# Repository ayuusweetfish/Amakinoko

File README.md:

# 天气蘑菇 · アマキノコ · Amakinoko

一个蘑菇外形的彩灯装置，流动的颜色依天气变化。光效亦可通过 USB 连接电脑定制。

[**汇报展示与视频**](https://ayuusweetfish.github.io/Amakinoko/)  
[**Rev. 2 资料**](https://github.com/ayuusweetfish/Amakinoko/releases/tag/rev-2)

## 食谱

材料
- 3D 打印外壳元件
- 炫彩纱布（？）
- WS2812/WS2812B 灯带（5050 灯珠；每米 96 灯，取 24 灯）
- 2.54 mm 排针
- 2.54 mm 跳线（杜邦线），双端孔头
- 组装电路板（PCBA）
- 胶水，如 UHU 胶
- （可选）热熔胶
- （可选）镀银纱线

步骤
1. 将纱布用胶水粘贴在两片外壳上；
2. 将 3 pin 排针焊接在灯带首端；
3. 将灯带打结成球状，尽可能使每一个朝向都有小灯；
4. 将灯带上的排针插入杜邦线，连接至电路板；
5. 将灯带与杜邦线固定在内胆内侧（可用胶水或热熔胶），保持灯带悬空在中央位置；
6. （可选）若有镀银纱线，可将其随意粘贴在外壳内壁，另一端穿过电路板上的触摸传感孔，打结、粘贴固定；
7. 将外壳与内胆粘贴固定；
8. 连接 USB 电源即可。

注：3D 打印与 PCBA 的组装未列入。PCBA 组装可参考 KiCad 工程文件；完成后通过 DAP 调试器向 STM32 微控制器写入固件，再通过蘑菇配置工具写入灯光程序。

## 定制灯光

通过 USB 数据线将装置连接至计算机，运行配置工具软件（发布页面提供 Windows 与 macOS 版本下载）。连接后即可看到实时读数、灯光颜色与光效程序。

光效程序运行在 [Mumu 虚拟机](./misc/mumu)中，目前以 Mumu 汇编语言撰写。Mumu 是一个结构简单的虚拟计算模型，其上的程序能访问 2 KiB 的内存空间。

## 目录组织
- **hw/**: 印刷电路板工程文件
- **fw/**: STM32 微控制器固件源程序
- **mech/**: 外壳 3D 模型
- **cfg/**: PC 配置工具软件源程序

部分文件可以通过以下软件打开（版本号作为参考）：
- 外壳：3D One
- 电路板：KiCad (7.0.10)
- 固件：Arm GNU Toolchain (GCC 10.3.1), STM32CubeG0 (1.5.0), PlatformIO (6.1.16)

## 许可

本仓库内的所有内容按照 CERN-OHL-S（CERN 开放硬件许可证第 2 版，强互惠条件）分发。完整原文参见 **COPYING.txt** 或[在线访问](https://ohwr.org/cern_ohl_s_v2.txt)。

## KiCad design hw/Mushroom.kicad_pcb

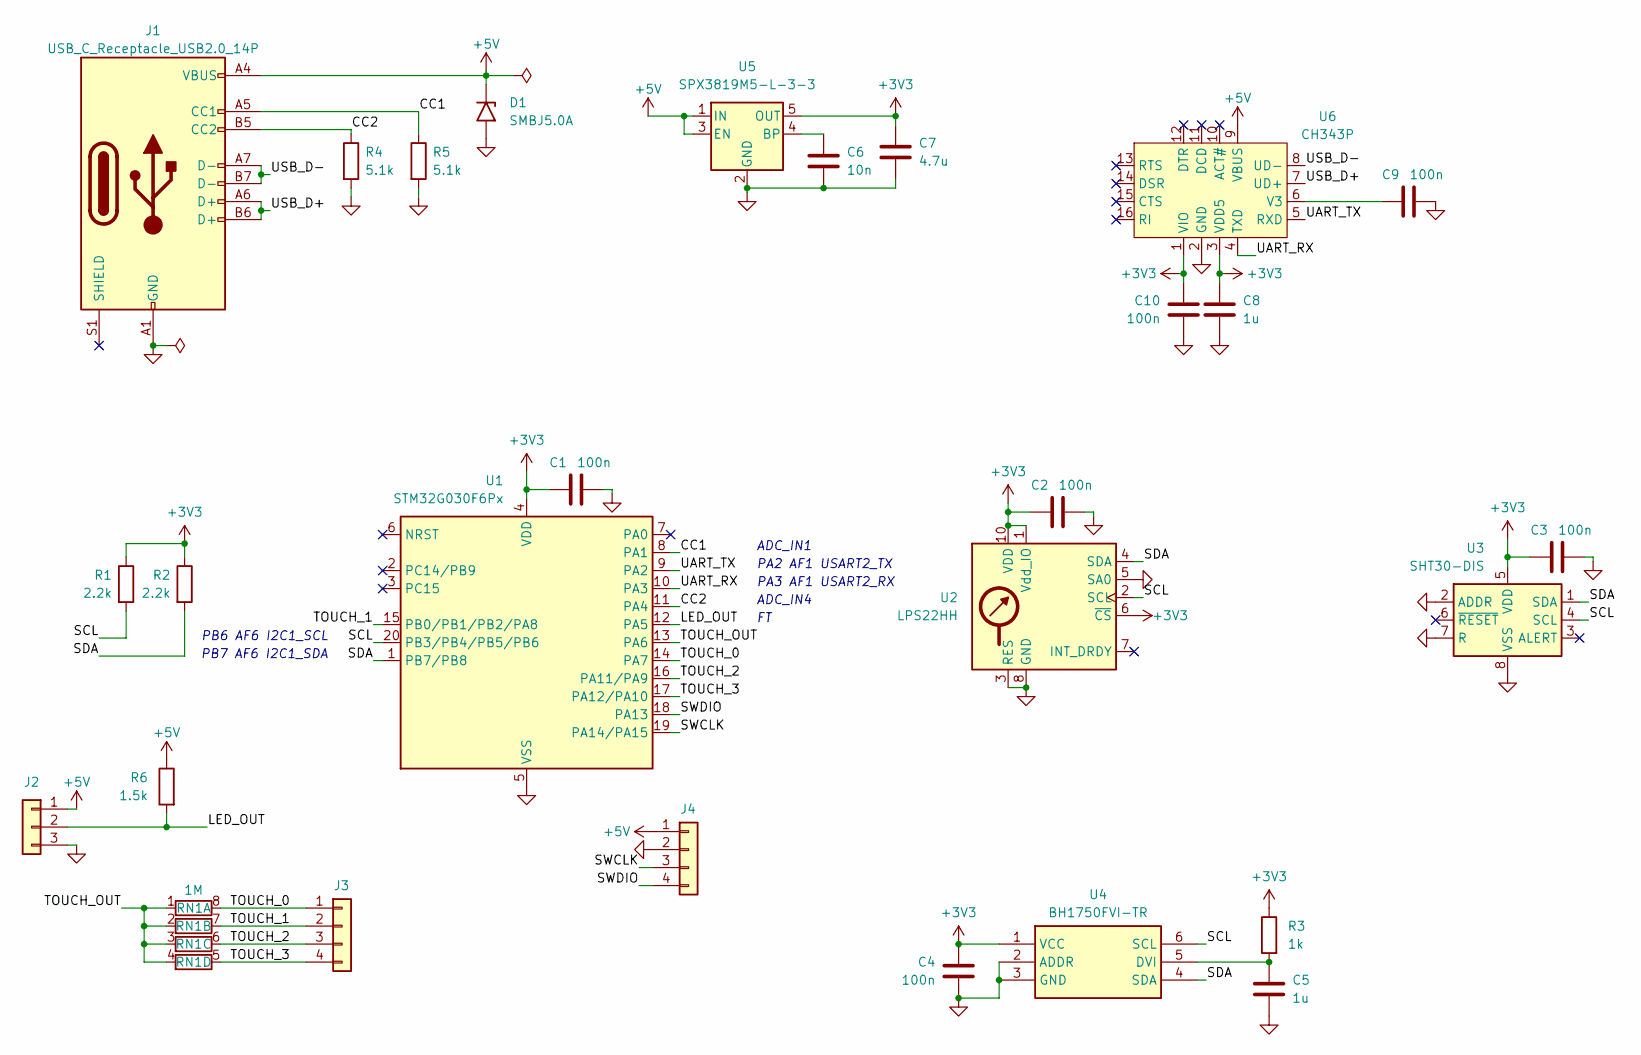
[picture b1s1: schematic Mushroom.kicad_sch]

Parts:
C1, C2, C3, C4, C9, C10: 100n; C_0402_1005Metric
C5, C8: 1u; C_0402_1005Metric
C6: 10n; C_0402_1005Metric
C7: 4.7u; C_0402_1005Metric
D1: SMBJ5.0A; D_SMB
J1: USB_C_Receptacle_USB2.0_14P; USB_C_Receptacle_HRO_TYPE-C-31-M-12
J2: Conn_01x03; PinHeader_1x03_P2.54mm_Vertical
J3: Conn_01x04; Arc_Pins_04
J4: Conn_01x04; TestPoints_1x04_P2.0
R1, R2: 2.2k; R_0402_1005Metric
R3: 1k; R_0402_1005Metric
R4, R5: 5.1k; R_0402_1005Metric
R6: 1.5k; R_0402_1005Metric
RN1: 1M; R_Array_Convex_4x0402
U1: STM32G030F6Px; TSSOP-20_4.4x6.5mm_P0.65mm
U2: LPS22HH; ST_HLGA-10_2x2mm_P0.5mm_LayoutBorder3x2y
U3: SHT30-DIS; Sensirion_DFN-8-1EP_2.5x2.5mm_P0.5mm_EP1.1x1.7mm
U4: BH1750FVI-TR; WSOF6; Manufacturer_Part_Number BH1750FVI-TR; Mouser Part Number 755-BH1750FVI-TR
U5: SPX3819M5-L-3-3; SOT-23-5
U6: CH343P; QFN-16-1EP_3x3mm_P0.5mm_EP1.9x1.9mm

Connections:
+3V3: C1.1, C2.1, C3.1, C4.1, C7.1, C8.1, C10.1, R1.1, R2.1, R3.1, U1.4 (VDD), U2.1 (Vdd_IO), U2.6 (~CS), U2.10 (VDD), U3.5 (VDD), U4.1 (VCC), U5.5 (OUT), U6.1 (VIO), U6.3 (VDD5)
+5V: D1.1 (A1), J1.A4 (VBUS), J1.A9 (VBUS), J1.B4 (VBUS), J1.B9 (VBUS), J2.1, J4.1, R6.1, U5.1 (IN), U5.3 (EN), U6.9 (VBUS)
/CC1: J1.A5 (CC1), R5.1, U1.8 (PA1)
/CC2: J1.B5 (CC2), R4.1, U1.11 (PA4)
/LED_OUT: J2.2, R6.2, U1.12 (PA5)
/SCL: R1.2, U1.20 (PB3/PB4/PB5/PB6), U2.2 (SCL), U3.4 (SCL), U4.6 (SCL)
/SDA: R2.2, U1.1 (PB7/PB8), U2.4 (SDA), U3.1 (SDA), U4.4 (SDA)
/SWCLK: J4.3, U1.19 (PA14/PA15)
/SWDIO: J4.4, U1.18 (PA13)
/TOUCH_0: J3.1, RN1.8 (R1.2), U1.14 (PA7)
/TOUCH_1: J3.2, RN1.7 (R2.2), U1.15 (PB0/PB1/PB2/PA8)
/TOUCH_2: J3.3, RN1.6 (R3.2), U1.16 (PA11/PA9)
/TOUCH_3: J3.4, RN1.5 (R4.2), U1.17 (PA12/PA10)
/TOUCH_OUT: RN1.1 (R1.1), RN1.2 (R2.1), RN1.3 (R3.1), RN1.4 (R4.1), U1.13 (PA6)
/UART_RX: U1.10 (PA3), U6.4 (TXD)
/UART_TX: U1.9 (PA2), U6.5 (RXD)
/USB_D+: J1.A6 (D+), J1.B6 (D+), U6.7 (UD+)
/USB_D-: J1.A7 (D-), J1.B7 (D-), U6.8 (UD-)
GND: C1.2, C2.2, C3.2, C4.2, C5.2, C6.2, C7.2, C8.2, C9.2, C10.2, D1.2 (A2), J1.A1 (GND), J1.A12 (GND), J1.B1 (GND), J1.B12 (GND), J2.3, J4.2, R4.2, R5.2, U1.5 (VSS), U2.3 (RES), U2.5 (SA0), U2.8 (GND), U2.9 (GND), U3.2 (ADDR), U3.7 (R), U3.8 (VSS), U3.9 (VSS), U4.2 (ADDR), U4.3 (GND), U5.2 (GND), U6.2 (GND), U6.17 (GND)
unnamed: C5.1, R3.2, U4.5 (DVI)
unnamed: C6.1, U5.4 (BP)
unnamed: C9.1, U6.6 (V3)

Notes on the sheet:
PB6 AF6 I2C1_SCL
PA2 AF1 USART2_TX
ADC_IN1
PA3 AF1 USART2_RX
ADC_IN4
PB7 AF6 I2C1_SDA

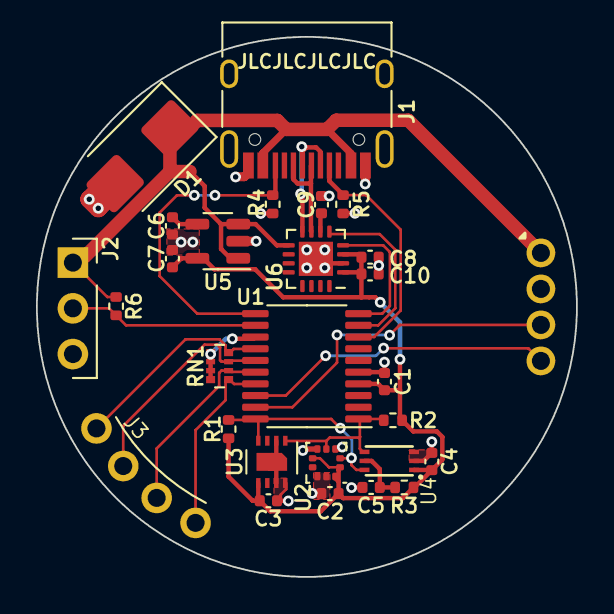
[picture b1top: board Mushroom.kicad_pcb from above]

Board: 2 copper layers, 30.0 x 30.0 mm, 28 parts (0 on the bottom side), 22 nets.

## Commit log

2024-10-16 🚧 Initial commit; empty hardware project
2024-10-18 Add testrun firmware (board is Curtain Rev. 1)
2024-10-19 Increase testrun light intensity & refresh rate
2024-10-21 Finish schematic
2024-10-21 🚧 Preliminary layout & routing
2024-10-21 Finish board design
2024-10-21 Revise and finalise board design
2024-10-21 🎉 Submit for fab (Rev. 1)
2024-10-21 Change board setup to white / 1 mm
2024-10-25 🎉 Initial firmware
2024-10-25 I2C SCL line stuck low?
2024-10-25 Toggle LED data output pin
2024-10-25 Restore I2C check
    Previous issue: BH1750FVI was soldered in the wrong direction
2024-10-25 ✨ Flowing lights!
2024-10-25 Fix I2C timing setting
2024-10-26 Read-out from LPS22HH
2024-10-26 Fix I2C bus stuck issue (output should be open-drain)
2024-10-26 Read-out from SHT30
2024-10-26 Revise board schematic
2024-10-26 Preliminary layout & routing
2024-10-26 🎉 Finalise design; submit for fab (Rev. 2)
2024-10-26 Fix TX/RX lines; re-submit for fab (Rev. 2)
    Previous order was cancelled (Y52, Y53)
2024-10-27 Clean-up of sensor-reading subroutine
2024-10-27 Incorporate sensor readings into the display loop
2024-10-27 Release WS2812 signal line when idle to avoid continuous draining current
2024-10-28 Implement capacitive sensing
2024-10-28 Incorporate capacitance sensing into main loop
2024-10-30 Add configuration GUI empty template
2024-10-30 Add Uxn in firmware
2024-10-30 Stress test Uxn
2024-10-31 🎉 A new VM??
2024-10-31 Optimise a bit 😈
2024-11-01 Computed goto (slower... T T)
2024-11-01 Small bug fixes
2024-11-01 Save new pattern generator for potential future demonstrations
2024-11-01 mumu: Implement load-store & branching instructions
2024-11-01 mumu: Fibonacci program
2024-11-01 mumu: Running Fibonacci on MCU
2024-11-01 mumu: Optimised Fibonacci
2024-11-01 mumu: Revise instruction set & documentation
2024-11-02 mumu: 🚧 Assembler
2024-11-02 mumu: 🚧 Parse mnemonics
2024-11-02 mumu: Parse all mnemonics and labels
2024-11-02 mumu: 🚧 Assemble most instructions
    TODO: memory, forward label patching
2024-11-02 mumu: 🎉 Assemble the Fibonacci program
2024-11-04 mumu: Correct platform-agnostic data width
2024-11-04 mumu-as: Refactor to report errors to caller routine
2024-11-04 mumu-as: Better error reporting
2024-11-04 mumu-as: Implement memory instructions
2024-11-04 mumu-as: Include column index in error report
2024-11-04 mumu-as: Support data directive
2024-11-04 mumu-as: Support absolute labels
2024-11-04 mumu-as: Support absolute branches
2024-11-04 mumu-as: Shorthand for unconditional branch
2024-11-04 mumu-as: Support comments
2024-11-04 fw: Adapt to both Rev. 1 and Rev. 2
2024-11-04 fw: Working UART
2024-11-05 cfg: Build with libserialport
2024-11-05 cfg: A first combo box...?
2024-11-05 cfg: 🚧 Non-working refresh... T T
2024-11-05 cfg: Working combo box with a patch
2024-11-05 cfg: Adapt changes to Windows build
2024-11-05 cfg: Fix indentation (use tab) in libui patch
2024-11-06 fw: Disable pagination in GDB
2024-11-06 fw: Sense CC pin voltage
2024-11-06 fw: Fix format-print warnings
2024-11-06 fw: Receive packets
2024-11-06 fw: Transmit state on request
2024-11-06 cfg: Check device signature
2024-11-06 fw, cfg: Increase baud rate to 921k6; misc. bug fixes
2024-11-07 cfg: Parse and display readings! 🎉
2024-11-07 fw: Continuously transmit readings after connection
2024-11-07 cfg: Parse continuous readings
2024-11-07 fw, cfg: Add tag to continuous readings payload
2024-11-07 cfg: Auto-refresh ports
2024-11-08 mumu: Add push/pop/call/ret to instruction set
2024-11-08 cfg: Replace with connect/disconnect button
2024-11-08 mumu-as: Refactor for reusable label handling logic
2024-11-08 mumu, mumu-as: Fully support stack operations
2024-11-09 fw, cfg: Fix handshake failure by correctly waiting for state reset
2024-11-09 mumu: Try lights
2024-11-09 mumu-as: Support hexadecimal numbers
2024-11-09 mumu: Toggling lights!
2024-11-09 mumu, mumu-as: Support 8-bit immediates in branching conditions
2024-11-09 mumu: Simplify lights program
2024-11-09 mumu-as: Add output format options
2024-11-09 fw: Erase/flash storage area
2024-11-09 fw: Write storage with fast programming mode
2024-11-10 fw, cfg: Transmit program binary and source from device
2024-11-10 fw, cfg: Load source text into GUI; add placeholder check/upload buttons
2024-11-11 fw, cfg: Refactor for better handling of messages
2024-11-11 fw: Eliminate IRQ disabling during touch sensing
    Cannot use DMA as we need to check each byte for its time of arrival. Or maybe use a flag and clear it often...? How to deal with ongoing transmissions at time of check in this case?
2024-11-11 fw: Eliminate IRQ blocks during LED write (🚧 untested)
2024-11-11 fw, cfg: Correctly uploading data! 🎉
2024-11-11 fw, cfg: Verify CRC after upload
2024-11-11 cfg: Add status bar for success messages
2024-11-11 fw: Fix error when uploading more than one row (256 bytes)
2024-11-11 cfg: 🚧 GUI redesign
2024-11-11 cfg: 🚧 GUI redesign (2/n)
2024-11-11 cfg: 🚧 GUI redesign (3/n)
2024-11-11 cfg: GUI redesign (done, hopefully)
2024-11-12 cfg: Draw disabled state dashboard when disconnected
2024-11-13 fw, cfg: Transmit flags indicating readings validity
2024-11-13 fw, mumu: Add timeout auto-stop
2024-11-13 mumu-as, cfg: Refactor assembler into separate header/source pair
2024-11-13 cfg: Assemble source
2024-11-13 mumu-as: Fix empty number literal is incorrectly accepted
2024-11-13 cfg: 🎉 Upload assembled binary and source!
2024-11-13 fw, cfg: Transmit and display light colours
2024-11-13 fw: 🎉 Run user programs for real!
2024-11-13 cfg: Fix buffer overflow bug
    Also checked against leaks, none found ^ ^
2024-11-14 cfg: Switch to monospaced typeface for code
2024-11-14 cfg: Resize window when folding/expanding
2024-11-14 mumu: Create lights emulator
2024-11-14 mumu: Move lights simulator to dedicated directory
2024-11-14 fw: Display pre-made pattern in case of timeout
2024-11-14 fw, cfg: Report timeout status in packet
2024-11-14 cfg: Hide data dumps behind a command line flag
2024-11-14 lights: Add new program 🚧
2024-11-14 lights: Separate R, G, B rather than compressed 🚧
2024-11-14 mumu: Add load/store two-register addressing mode
2024-11-14 lights: Fade between consecutive lights
2024-11-14 fw: Fix WS281x timing glitches
2024-11-14 fw: Fix incorrect stack pointer after upload
    Generates spurious timeouts
2024-11-14 fw: Reset entire Mumu RAM (thus program state) after a timeout
2024-11-15 cfg: Adjust colour display
2024-11-15 cfg: Fix Windows build
2024-11-15 fw, cfg: Transmit unique ID at handshake; add firmware release mode
2024-11-15 fw: Check CRC for SHT30 data
2024-11-15 cfg: Flush serial buffer before sending handshake message
    In case a message from an unterminated previous connexion arrives. This might reduce failure by a bit, but anyway, the best solution is to connect ACT#...
2024-11-15 lights: Flowing lights 🚧 (too fast!)
2024-11-15 lights: More smooth fading (but too slow?)
2024-11-15 lights: Flowing rainbows again, this time with Mumu! 🌈✨
2024-11-15 cfg: Compress source code with zlib
2024-11-15 fw: Properly reset VM if flash write occurs midway
2024-11-15 fw: Do not include debugging packets in production
2024-11-15 docs: Add preliminary README
2024-11-15 docs: Add directory structure and licence to README
2024-11-16 cfg: Do not fail on source decompression error
2024-11-16 mech: Add casing
2024-11-16 docs: Add image
2024-11-16 cfg: Building on Windows 🎉
2024-11-16 cfg: Tweak status notification scheme
2024-11-16 🎉 Slides
2024-11-16 Add keyboard navigation
2024-11-16 docs: A lot of documentation. Pinned for release 🎉
2024-11-17 Remove duplicate image
